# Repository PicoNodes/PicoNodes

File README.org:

* We have moved!

This project has a new home, over at https://gitlab.com/PicoNodes/PicoNodes

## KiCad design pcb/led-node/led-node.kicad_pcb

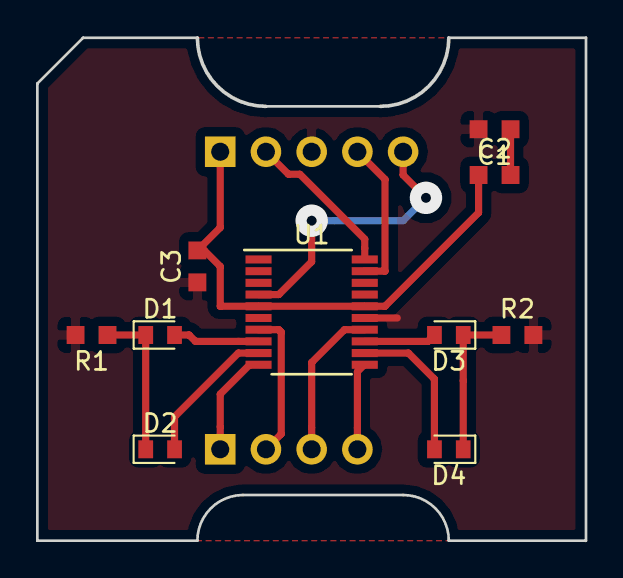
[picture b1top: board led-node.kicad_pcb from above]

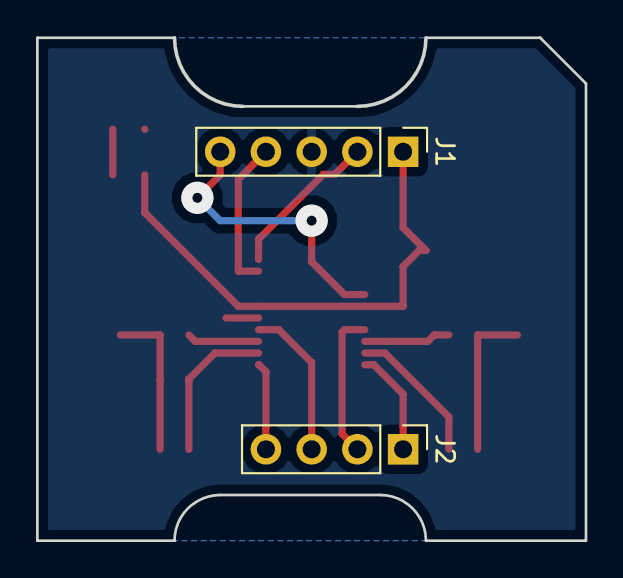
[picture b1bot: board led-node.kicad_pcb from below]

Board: 2 copper layers, 30.4 x 27.9 mm, 12 parts (2 on the bottom side), 16 nets.

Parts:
C1, C2: 100nF; C_0603_1608Metric_Pad0.99x1.00mm_HandSolder
C3: 10nF; C_0603_1608Metric_Pad0.99x1.00mm_HandSolder
D1: LED1; LED_0603_1608Metric_Pad0.82x1.00mm_HandSolder
D2: LED2; LED_0603_1608Metric_Pad0.82x1.00mm_HandSolder
D3: LED3; LED_0603_1608Metric_Pad0.82x1.00mm_HandSolder
D4: LED4; LED_0603_1608Metric_Pad0.82x1.00mm_HandSolder
J1: STM32_SWD; PinHeader_1x05_P2.54mm_Vertical
J2: PicoTalk; PinHeader_1x04_P2.54mm_Vertical
R1, R2: 100; R_0603_1608Metric_Pad0.99x1.00mm_HandSolder
U1: STM32F030F4Px; TSSOP-20_4.4x6.5mm_P0.65mm

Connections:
/Down: J2.1, U1.10
/Left: J2.2, U1.7
/Right: J2.4, U1.11
/SWCLK: J1.2, U1.20
/SWDIO: J1.4, U1.19
/Up: J2.3, U1.14
/nRST: J1.5, U1.4
GND: C1.2, C3.1, J1.3, R1.2, R2.2, U1.15
unnamed: C1.1, C2.2
unnamed: D1.1, D2.1, R1.1
unnamed: D1.2, U1.8
unnamed: D2.2, U1.9
unnamed: D3.1, D4.1, R2.1
unnamed: D3.2, U1.13
unnamed: D4.2, U1.12
VDD: C2.1, C3.2, J1.1, U1.5, U1.16

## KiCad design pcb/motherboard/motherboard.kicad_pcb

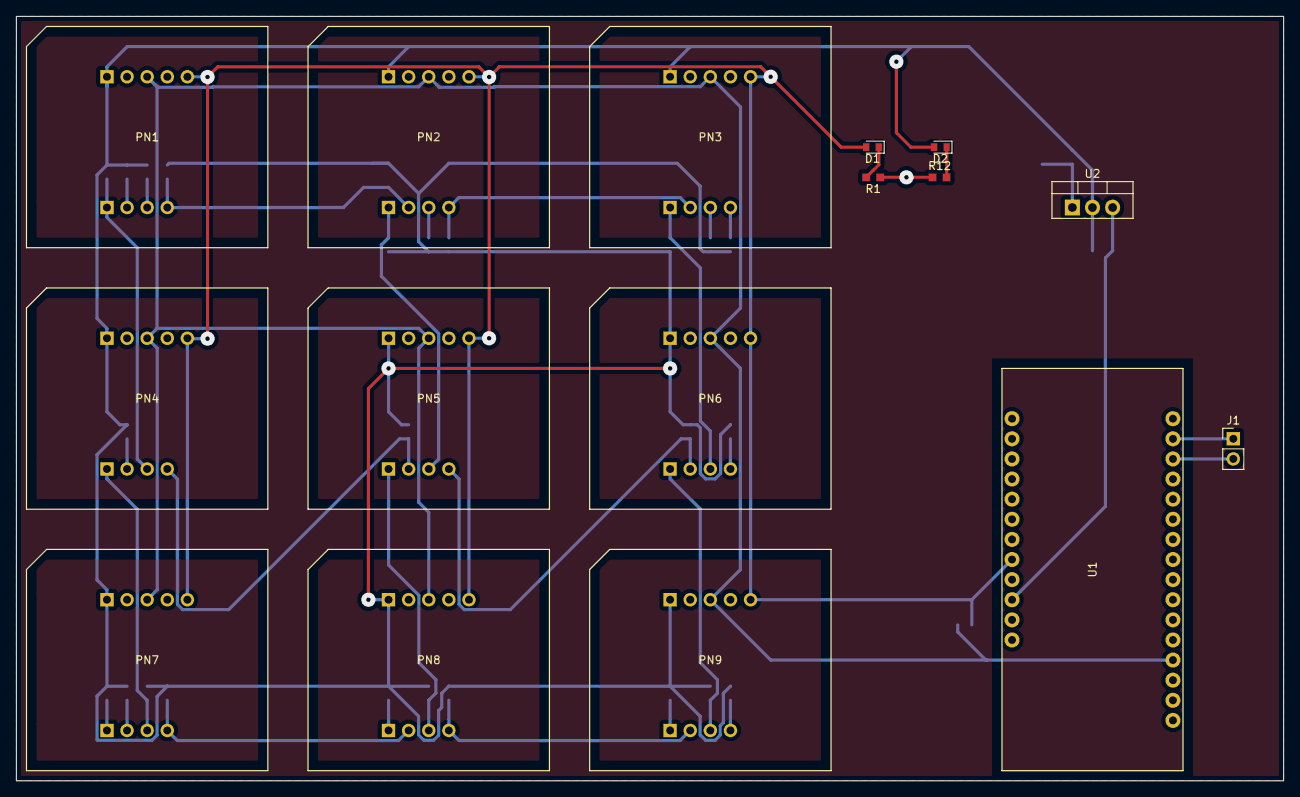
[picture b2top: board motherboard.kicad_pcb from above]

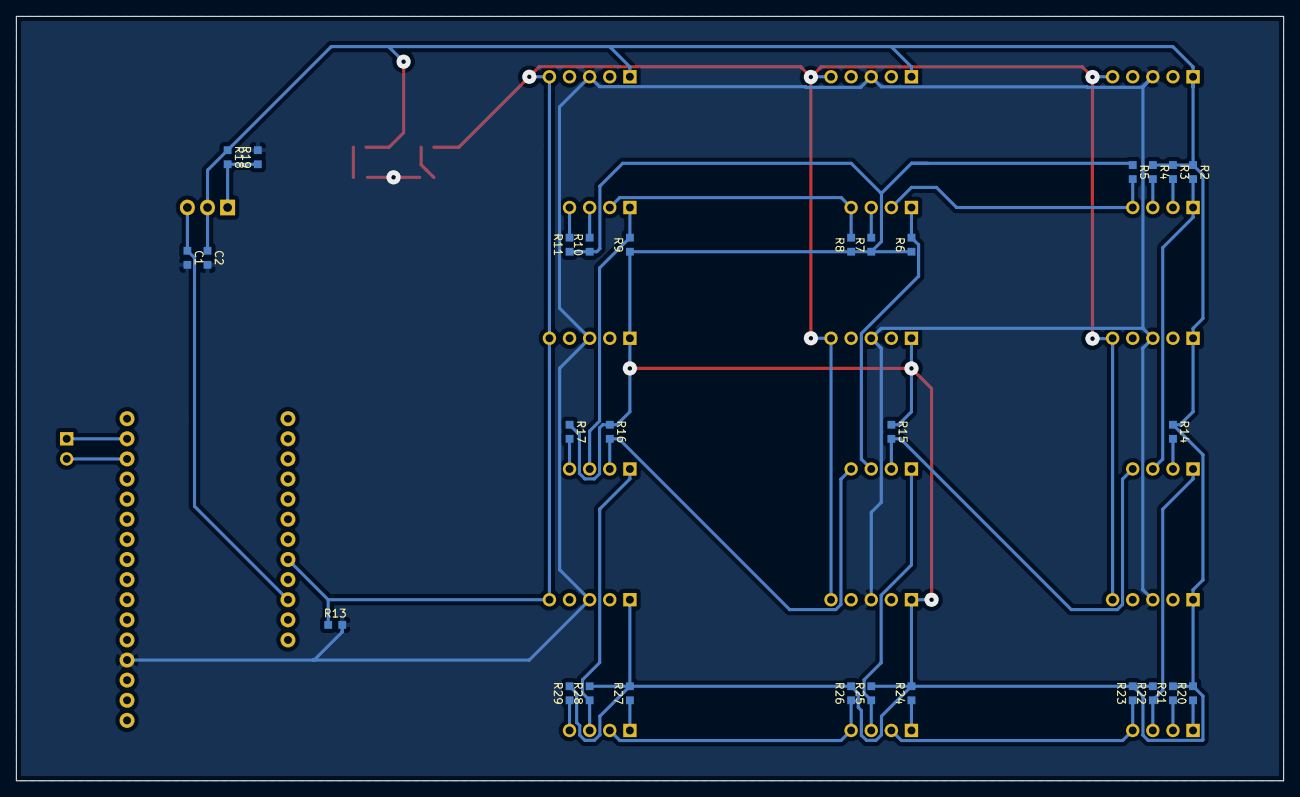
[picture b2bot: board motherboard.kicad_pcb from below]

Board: 2 copper layers, 160.0 x 96.5 mm, 45 parts (29 on the bottom side), 33 nets.

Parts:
C1: 0.1µF; C_0603_1608Metric_Pad0.99x1.00mm_HandSolder
C2: 1.0µF; C_0603_1608Metric_Pad0.99x1.00mm_HandSolder
D1: LED_Reset; LED_0603_1608Metric_Pad0.82x1.00mm_HandSolder
D2: LED_Vdd; LED_0603_1608Metric_Pad0.82x1.00mm_HandSolder
J1: UART; PinHeader_1x02_P2.54mm_Vertical
PN1, PN2, PN3, PN4, PN5, PN6, PN7, PN8, PN9: PicoNode-Socket-PH
R1, R12: 100; R_0603_1608Metric_Pad0.99x1.00mm_HandSolder
R2, R3, R4, R5, R6, R7, R8, R9, R10, R11, R14, R15, R16, R17, R20, R21, R22, R23, R24, R25, R26, R27, R28, R29: 4.7K; R_0603_1608Metric_Pad0.99x1.00mm_HandSolder
R13: 820; R_0603_1608Metric_Pad0.99x1.00mm_HandSolder
R18: 240; R_0603_1608Metric_Pad0.99x1.00mm_HandSolder
R19: 390; R_0603_1608Metric_Pad0.99x1.00mm_HandSolder
U1: Huzzah32; Adafruit_HUZZAH32
U2: LM317_3PinPackage; TO-220-3_Vertical

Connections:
/RX: J1.2, U1.26
/TX: J1.1, U1.27
/nReset: D1.2, PN1.5, PN2.5, PN3.5, PN4.5, PN5.5, PN6.5, PN7.5, PN8.5, PN9.5, R13.1, U1.5
GND: C1.2, C2.2, PN1.3, PN2.3, PN3.3, PN4.3, PN5.3, PN6.3, PN7.3, PN8.3, PN9.3, R1.1, R12.1, R13.2, R19.2, U1.16
unnamed: D1.1, R1.2
unnamed: D2.1, R12.2
unnamed: PN1.6, PN4.8, R2.2
unnamed: PN1.7, R3.2
unnamed: PN1.8, R4.2
unnamed: PN1.9, PN2.7, R5.2
unnamed: PN2.6, PN5.8, R6.2
unnamed: PN2.8, R7.2
unnamed: PN2.9, PN3.7, R8.2
unnamed: PN3.6, PN6.8, R9.2
unnamed: PN3.8, R10.2
unnamed: PN3.9, R11.2
unnamed: PN4.6, PN7.8, R22.1
unnamed: PN4.7, R14.2
unnamed: PN4.9, PN5.7, R15.2
unnamed: PN5.6, PN8.8, R25.1
unnamed: PN5.9, PN6.7, R16.2
unnamed: PN6.6, PN9.8, R28.1
unnamed: PN6.9, R17.2
unnamed: PN7.6, R20.1
unnamed: PN7.7, R21.1
unnamed: PN7.9, PN8.7, R23.1
unnamed: PN8.6, R24.1
unnamed: PN8.9, PN9.7, R26.1
unnamed: PN9.6, R27.1
unnamed: PN9.9, R29.1
unnamed: R18.2, R19.1, U2.1
VBUS: C1.1, U1.3, U2.3
VDD: C2.1, D2.2, PN1.1, PN2.1, PN3.1, PN4.1, PN5.1, PN6.1, PN7.1, PN8.1, PN9.1, R2.1, R3.1, R4.1, R5.1, R6.1, R7.1, R8.1, R9.1, R10.1, R11.1, R14.1, R15.1, R16.1, R17.1, R18.1, R20.2, R21.2, R22.2, R23.2, R24.2, R25.2, R26.2, R27.2, R28.2, R29.2, U2.2

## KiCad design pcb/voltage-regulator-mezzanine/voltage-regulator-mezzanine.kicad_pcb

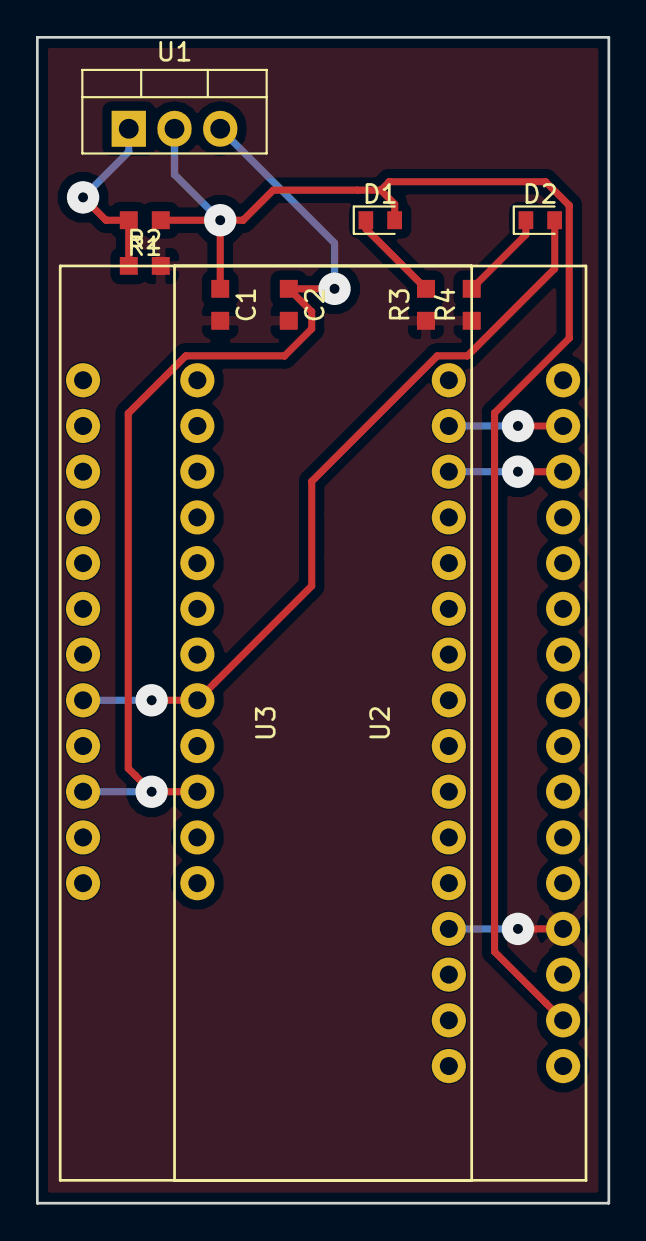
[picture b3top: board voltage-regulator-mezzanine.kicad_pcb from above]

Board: 2 copper layers, 31.8 x 64.8 mm, 11 parts (0 on the bottom side), 9 nets.

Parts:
C1: 1.0µF; C_0603_1608Metric_Pad0.99x1.00mm_HandSolder
C2: 0.1µF; C_0603_1608Metric_Pad0.99x1.00mm_HandSolder
D1: LED_vdd; LED_0603_1608Metric_Pad0.82x1.00mm_HandSolder
D2: LED_nReset; LED_0603_1608Metric_Pad0.82x1.00mm_HandSolder
R1: 240; R_0603_1608Metric_Pad0.99x1.00mm_HandSolder
R2: 390; R_0603_1608Metric_Pad0.99x1.00mm_HandSolder
R3, R4: 100; R_0603_1608Metric_Pad0.99x1.00mm_HandSolder
U1: LM317_3PinPackage; TO-220-3_Vertical
U2: Huzzah32_fake; Adafruit_HUZZAH32
U3: Huzzah32_real; Adafruit_HUZZAH32

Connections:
/Adj: R1.2, R2.1, U1.1
GND: C1.2, C2.2, R2.2, R3.1, R4.1, U2.16, U3.16
unnamed: D1.1, R3.2
unnamed: D2.1, R4.2
unnamed: D2.2, U2.5, U3.5
unnamed: U2.26, U3.26
unnamed: U2.27, U3.27
VBUS: C2.1, U1.3, U2.3, U3.3
VDD: C1.1, D1.2, R1.1, U1.2, U2.14

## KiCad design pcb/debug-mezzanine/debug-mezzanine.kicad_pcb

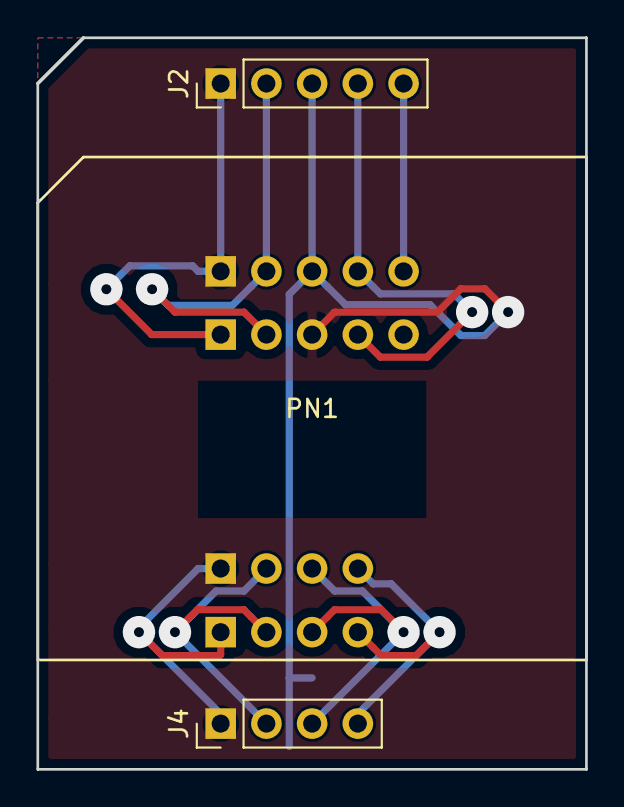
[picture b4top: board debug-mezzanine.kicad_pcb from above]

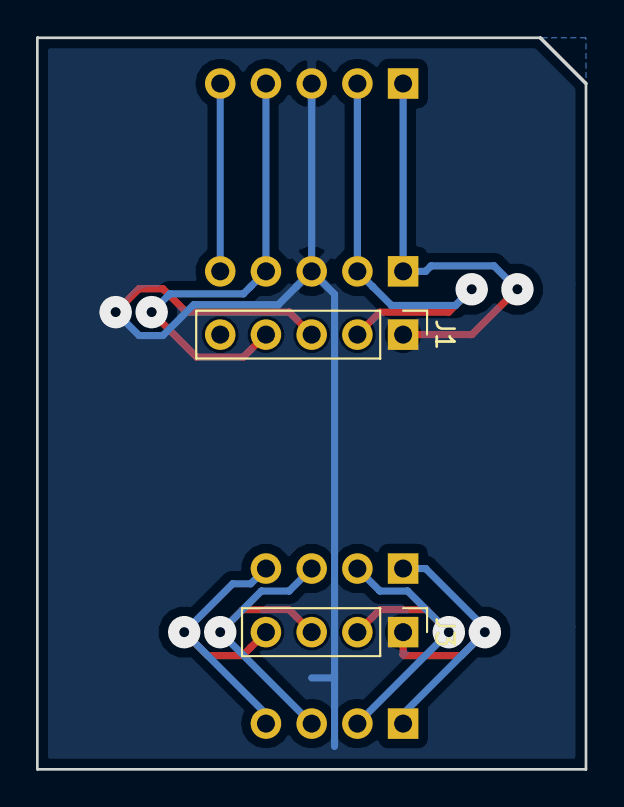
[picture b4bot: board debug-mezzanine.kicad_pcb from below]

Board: 2 copper layers, 30.5 x 40.6 mm, 5 parts (2 on the bottom side), 9 nets.

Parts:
J1, J2: STM32_SWD; PinHeader_1x05_P2.54mm_Vertical
J3, J4: PicoTalk; PinHeader_1x04_P2.54mm_Vertical
PN1: PicoNode-Socket-PH

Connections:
GND: J1.3, J2.3, PN1.3
unnamed: J1.2, J2.2, PN1.2
unnamed: J1.4, J2.4, PN1.4
unnamed: J2.5, PN1.5
unnamed: J3.1, J4.1, PN1.6
unnamed: J3.2, J4.2, PN1.7
unnamed: J3.3, J4.3, PN1.8
unnamed: J3.4, J4.4, PN1.9
VDD: J1.1, J2.1, PN1.1

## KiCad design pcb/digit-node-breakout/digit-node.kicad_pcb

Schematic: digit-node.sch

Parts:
C1, C2, C3: CP; C_0603_1608Metric
J1: Conn_01x09_Male; PinHeader_1x09_P2.54mm_Vertical
J2: STM32_SWD; PinHeader_1x05_P2.54mm_Vertical
Q1: BC847BS; SOT-363_SC-70-6
R1, R2: 100; R_0603_1608Metric
U1: STM32F030F4Px; TSSOP-20_4.4x6.5mm_P0.65mm

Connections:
/led_matrix/gnd_even: R2.1; also elsewhere on the board
/led_matrix/gnd_odd: R1.1; also elsewhere on the board
/led_matrix/led_01: U1.14; also elsewhere on the board
/led_matrix/led_23: U1.8; also elsewhere on the board
/led_matrix/led_45: U1.9; also elsewhere on the board
/led_matrix/led_67: U1.12; also elsewhere on the board
/led_matrix/led_89: U1.13; also elsewhere on the board
GND: C1.2, C3.2, J1.1, J2.3, Q1.1 (E1), Q1.4 (E2), U1.15
unnamed: C2.2, C3.1
unnamed: J1.4, U1.6
unnamed: J1.5, U1.3
unnamed: J1.6, U1.2
unnamed: J1.7, U1.7
unnamed: J1.8, U1.17
unnamed: J1.9, U1.18
unnamed: J2.2, U1.20
unnamed: J2.4, U1.19
unnamed: J2.5, U1.4
unnamed: Q1.2 (B1), U1.10
unnamed: Q1.3 (C2), R2.2
unnamed: Q1.5 (B2), U1.11
unnamed: Q1.6 (C1), R1.2
VDD: C1.1, J1.2, J2.1, U1.16
VDDA: C2.1, J1.3, U1.5

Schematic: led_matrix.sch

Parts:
D1: LED_0; LED_0603
D2: LED_1; LED_0603
D3: LED_2; LED_0603
D4: LED_3; LED_0603
D5: LED_4; LED_0603
D6: LED_5; LED_0603
D7: LED_6; LED_0603
D8: LED_7; LED_0603
D9: LED_8; LED_0603
D10: LED_9; LED_0603

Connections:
/led_matrix/gnd_even: D2.1, D4.1, D6.1, D8.1, D10.1; also elsewhere on the board
/led_matrix/gnd_odd: D1.1, D3.1, D5.1, D7.1, D9.1; also elsewhere on the board
/led_matrix/led_01: D1.2, D2.2; also elsewhere on the board
/led_matrix/led_23: D3.2, D4.2; also elsewhere on the board
/led_matrix/led_45: D5.2, D6.2; also elsewhere on the board
/led_matrix/led_67: D7.2, D8.2; also elsewhere on the board
/led_matrix/led_89: D9.2, D10.2; also elsewhere on the board

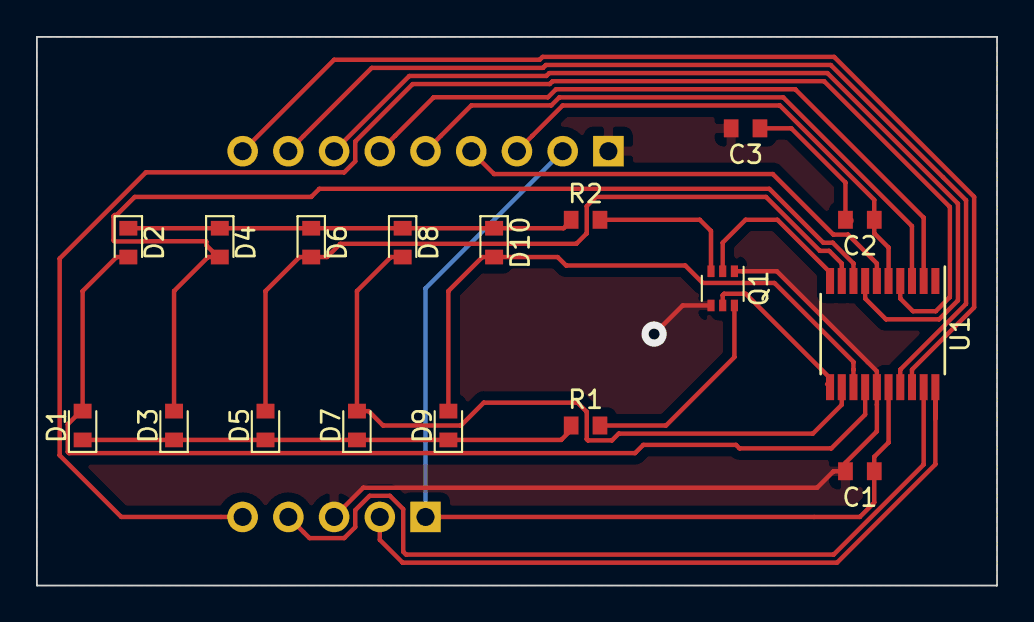
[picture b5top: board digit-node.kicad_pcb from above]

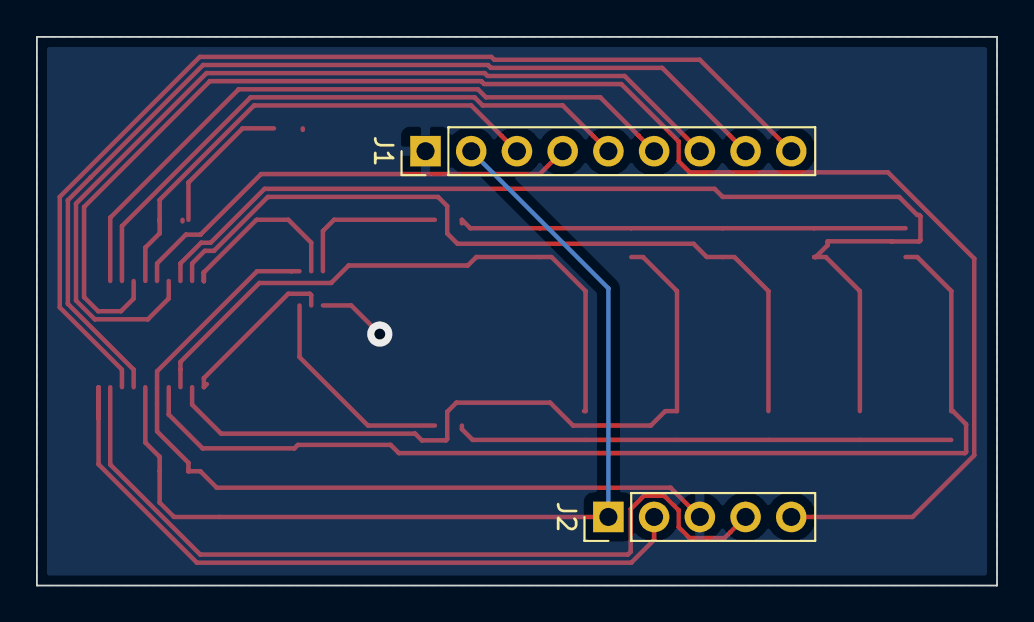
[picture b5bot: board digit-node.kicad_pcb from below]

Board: 2 copper layers, 53.3 x 30.5 mm, 19 parts (2 on the bottom side), 24 nets.

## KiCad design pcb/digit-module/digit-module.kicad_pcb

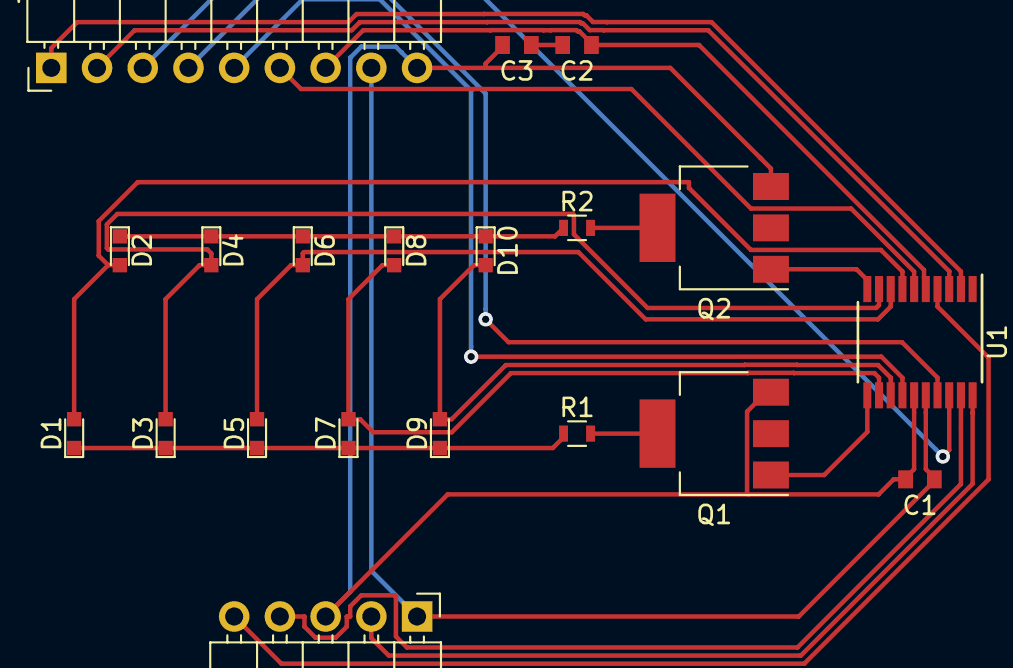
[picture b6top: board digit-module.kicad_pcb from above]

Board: 2 copper layers, 20 parts (0 on the bottom side), 24 nets.

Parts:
C1, C2, C3: CP; C_0603_1608Metric
D1: LED_0; LED_0603
D2: LED_1; LED_0603
D3: LED_2; LED_0603
D4: LED_3; LED_0603
D5: LED_4; LED_0603
D6: LED_5; LED_0603
D7: LED_6; LED_0603
D8: LED_7; LED_0603
D9: LED_8; LED_0603
D10: LED_9; LED_0603
J1: Conn_01x09_Male; PinHeader_1x09_P2.54mm_Horizontal
J2: STM32_SWD; PinHeader_1x05_P2.54mm_Horizontal
Q1, Q2: PZT2222A; SOT-223-3_TabPin2
R1, R2: 100; R_0603
U1: STM32F030F4Px; TSSOP-20_4.4x6.5mm_Pitch0.65mm

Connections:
/led_matrix/gnd_even: D2.1, D4.1, D6.1, D8.1, D10.1, R2.1
/led_matrix/gnd_odd: D1.1, D3.1, D5.1, D7.1, D9.1, R1.1
/led_matrix/led_01: D1.2, D2.2, U1.7
/led_matrix/led_23: D3.2, D4.2, U1.9
/led_matrix/led_45: D5.2, D6.2, U1.8
/led_matrix/led_67: D7.2, D8.2, U1.12
/led_matrix/led_89: D9.2, D10.2, U1.13
GND: C1.2, C3.2, J1.9, J2.3, Q1.3, Q2.3, U1.15
unnamed: C2.2, C3.1
unnamed: J1.1, U1.2
unnamed: J1.2, U1.3
unnamed: J1.3, U1.18
unnamed: J1.4, U1.17
unnamed: J1.5, U1.14
unnamed: J1.6, U1.6
unnamed: J2.2, U1.20
unnamed: J2.4, U1.19
unnamed: J2.5, U1.4
unnamed: Q1.1, U1.11
unnamed: Q1.2, R1.2
unnamed: Q2.1, U1.10
unnamed: Q2.2, R2.2
VDD: C1.1, J1.8, J2.1, U1.16
VDDA: C2.1, J1.7, U1.5

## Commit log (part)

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2018-03-19 Directory structure
2018-03-20 Added design notes and PCB sketch
2018-03-20 Moved design docs to docs folder
2018-03-20 ISA draft
2018-03-20 First prototype of assembler
2018-03-20 Allow empty lines, comments prototype
2018-03-21 Project structure for IDE
2018-03-21 greberfiler
    Alla gerberfiler som kan tänkas behövas för att fräsa PCB
2018-03-21 Started playing around with embedded rust for firmware
2018-03-21 Scala.js scaffolding
2018-03-22 Initial draft of UI that shows parser output and does light autoformatting
2018-03-22 Made autoformatting less overzealous
2018-03-23 Added outline for picoide server side, added support for stylesheets
2018-03-23 Monospace code editor
2018-03-26 Fixed the bytecode viewer
2018-03-26 Various cleanup
2018-03-26 Started playing around with node clients
2018-03-26 PCB and method in report
    beginning of method in the report
2018-03-26 More work on NodeServer
2018-03-27 Added a registry for connected nodes
2018-03-28 IDE: Use BooPickle for serialization
2018-03-29 IDE: Started integrating IDEClient
    Currently broken because Sink.actorRefWithAck causes linking errors,
    investigating alternative solutions
2018-03-29 IDE: Rewrote WSClient as a GraphStage instead of an Actor
2018-03-29 IDE: Sped up rebuild time dramatically
2018-03-29 Enable source maps, allow running in fullopt mode
2018-03-29 Cleaned up some side effects
2018-03-29 Added dependency graph plugin
2018-03-30 Removed a bunch of dead messages
2018-03-30 IDE: Heartbeats, don't hang after the first message
2018-03-30 IDE: Handle client-side event handling errors
2018-03-30 IDE: Don't beat so loudly
2018-03-30 Don't log raw IDE messages
2018-03-30 Implemented node list subscription
    Fixes #14
2018-03-31 Automatically subscribe to the node list
2018-03-31 Updated ENSIME
2018-03-31 Fixed Webpack refusing to build unless both fastopt and opt entrypoints were available
2018-03-31 Client-side board selection
2018-04-01 Kill the connection properly when the server fails to handle an incoming request
2018-04-01 Cleaned up build definition
2018-04-04 module and project updates
    module and report updates
2018-04-05 Swappable flow adapter
2018-04-05 Migrated to a separate IDECommandHandler stage
2018-04-05 Renamed all references for Programmers to Downloaders, according to #15
2018-04-05 Don't show the downloader change before it's actually done
2018-04-05 More lenses
2018-04-09 Syntax highlighting
2018-04-10 Added terminology document, fixes #15
2018-04-10 Cleaned up terminology doc a bit
2018-04-11 testcodes and dic
    for mcu questionformular
2018-04-11 LED blinker for F0 MCU
2018-04-11 Clarify the role of PicoStorm
2018-04-11 docs
    architecture, picture of comflow
2018-04-11 Added downloader version command/event
2018-04-11 Moved platform architecture diagram to Ditaa
2018-04-11 Mention the IDE in the platform architecture diagram
    Fixes #10
2018-04-11 Get rid of Word architecture diagram
2018-04-11 UX for downloading a program
2018-04-11 Support for emitting DownloadBytecode DownloaderCommands
2018-04-12 Added page 2 of questionaire
2018-04-13 Emacs: don't build tests for blinky
2018-04-13 Moved stm32f0x0 to https://github.com/PicoNodes/stm32f0x0
2018-04-13 Renamed BoardPicker to DownloaderPicker
2018-04-13 Imported ESP32 hello world
2018-04-13 Started playing around with downloader
2018-04-14 Register- and libfile
    Started the actionfunctions for the intructions. This file compile :)
2018-04-14 Reg- and libfile
    I forgot to save. This is compiling
2018-04-14 Ok this is going to compile!
    last try
2018-04-16 Got rid of some hello world code in the downloader
2018-04-16 Ignore more temp files from ESP-IDF
2018-04-16 Repport
    The methology chapter, an introduction.
2018-04-16 Diode-React has now released a ScalaJS-React 1.2 build, so we no longer need to rebuild it ourselves
2018-04-16 Couple error handling for DownloaderServer
2018-04-16 TLS for Server<->Downloader communication
2018-04-16 Split up picoserver according to a rough layer structure
2018-04-17 Report
    Methology chapter
2018-04-17 TLSClientAuthStage: Don't double-pull
2018-04-17 Background
    Making a summery of studies made for the implementation of datalogical
    thinking and programming in scool.
2018-04-17 Fixed downloaders being deregistered immediately
2018-04-17 Added pseudocode implementations of instructions to ISA
2018-04-17 Implemented the other instructions in the assembler
2018-04-17 Reenabled BytecodeViewer, see #25
2018-04-17 Show errors inline, see #25
2018-04-17 Report
    Background
2018-04-17 Show widgets for all errors, not just the first, fixes #25
2018-04-17 Styling for assembler errors
2018-04-17 Disabled BytecodeViewer
2018-04-17 Netclient can now connect and auth
2018-04-17 Refactored netclient to be easier to integrate
2018-04-17 Don't build main for standalone netclient
2018-04-17 picorunner.rs
    Work on func run instruction
2018-04-17 netclient on ESP32 now sorta kinda maybe works
2018-04-18 Report
    Report
2018-04-18 Server<->Downloader communication is also PicoStorm
2018-04-18 New doc
    Digitaliseringskommisionens statliga utredning om att digitalisera
    Sverige och med det IT-politiska målet att göra Sverige bäst i världen
    på att använda digitaliseringen möjligheter.
2018-04-18 Timeout for downloaders that are stuck authenticating
2018-04-18 Renamed hello_world_main.c
2018-04-18 MCU programming
    Work on the interpreter and running instructions. This compile. Next is
    to make testfunctions to see evrything run correctly
2018-04-18 Added read function to netclient
2018-04-18 Downloader can now communicate over UART!
2018-04-19 Instructions and PicoTalk
    Finnished the program for running the instructions and started
    documenting PicoTalk protocol.
2018-04-19 Started the domcs for PicoTalk protocol
2018-04-19 Integrated timing diagram into PicoTalk.org
2018-04-19 Finished PicoTalk timing diagram
2018-04-19 Implemented opendrainy in terms of the HAL
2018-04-19 Starting write to pin. Compiling
2018-04-20 Spellcheck
2018-04-20 PicoStorm: added support for writing events
2018-04-20 Described PicoStorm so far
    Fixes #22
2018-04-20 Compiles
2018-04-20 Attempted to rewrite opendrainy using RTFM
2018-04-20 Removed some test data
2018-04-23 Fixed opendrainy-rtfm not firing USART interrupts
2018-04-23 arithOp should be 1 for sub, not 0
2018-04-23 PicoStorm: Report invalid message IDs
2018-04-23 Print received PicoStorm commands
2018-04-23 Mention empty PicoStorm messages in the spec
2018-04-23 PicoStorm ping messages, fixes #27
2018-04-24 Updated client keys to follow the new DN scheme
2018-04-24 Downloader labels!
2018-04-24 Finnished reading pin. Compiles
2018-04-27 Added Picotalk transmitter FSM
2018-04-27 Transmit statemachine
2018-04-27 Added piconode-compute and picostore subprojects
2018-04-27 Moving main to piconode-compute
2018-04-27 Writing to flash sorta kinda works, ish
2018-04-30 Fixed flash memory writes
    Fixes #29
2018-04-30 Renamed USART1 task to something more appropriate
2018-04-30 Naming cleanup
2018-04-30 Forward checksum to IDE
    See #32
2018-04-30 Moved breakout board to separate subfolder
2018-04-30 Added Digit Node schematic draft
2018-05-01 Renamed digit-module for consistency
2018-05-01 More digit PCB cleanup
2018-05-01 Digit PCB is now 100% via-free!
2018-05-01 Even more compact!
2018-05-01 Oops.. missed a stale track screwing with things
2018-05-01 Blacklisted more backup files
2018-05-01 Ground planes
2018-05-01 Board outline
2018-05-01 Documented how to get STL files out of KiCad
2018-05-02 PCB cavity for enclosure
2018-05-02 Finnish Recieve machine state. This compiles
2018-05-02 Use a transistor array instead of two discrete transistors
2018-05-02 updates on recieve fn. Compiles
    May add changes to add a last state. Transmission done with the recieved
    value
2018-05-02 module for more flash pcb. Not tested
2018-05-03 Some comments on the pico-commpute srcfile
2018-05-03 Adapted PCB for Mentorspace mill design rules
2018-05-04 Finnished picotalk and started node communication task and path
2018-05-04 Piconodes test tasks
2018-05-04 Digit demo
2018-05-07 Started working on a the node motherboard...
2018-05-07 Adopted compute node PCB to use pin headers
    Since we currently don't have any 1mm PCB stock to use
2018-05-07 LED and button node PCBs
2018-05-07 Try for transmit and recieve. This do not work
2018-05-08 Fixed invalid diagrams
2018-05-08 Communication protocol
    Compiles and uses 10k Hz
2018-05-08 Started merging the compute node code
2018-05-08 Increased auth timeout
2018-05-08 More integration stuff
2018-05-08 Node-programmer
2018-05-08 piconode-led
2018-05-08 Pin orientation
2018-05-09 More convenient flashing
2018-05-09 Converted prog_counter to usize
2018-05-10 datasheet for the piconode-led
2018-05-10 File browser
2018-05-10 Spelling
2018-05-11 User manual for the piconode-switch
2018-05-11 Prepared piconode-led and -switch for the "real" node boards
2018-05-14 Made PicoNode-LED resync the PicoTalk clock at the beginning of each message
    This allows stable communication at 10kHz
2018-05-14 Debug mezzanine PCB
2018-05-14 user example
    Doc procoded with example for the user to program one piconode and use
    it with the lednode and the switchnode
2018-05-15 iomem instructions
2018-05-15 Use the ground plane, Luke!
2018-05-15 Fixed a race condition in LED<->Switch communication
2018-05-16 Moved rename to clicking the name
2018-05-16 Suggest saving before switching file
2018-05-16 Made the save prompt (slightly) prettier
2018-05-16 Added a prompt when trying to leave without saving
2018-05-16 Updated dependencies
2018-05-16 Factored out modality to a separate component
2018-05-16 Fixed "ghost" errors appearing when opening files
    Fixes #36
2018-05-16 Reformat the current line on blur
2018-05-16 Reduced log spam
2018-05-17 Bring our own voltage regulator instead of using the Huzzah32's built-in
2018-05-17 Via optimization
2018-05-17 Track cleanup
2018-05-17 Nicer motherboard markings
2018-05-17 We definitely need a heat sink...
2018-05-17 IGNORE
2018-05-18 picoregister
    modified the register to integrate the system
2018-05-18 picorunner
2018-05-18 Make the DRC happy
2018-05-18 Moved LED node text
2018-05-18 Voltage regulator mezzanine
    Got to bodge it since we don't have the PCB area to make another new motherboard
    Vbus is still forwarded, so it will still work (although have no real use) with
    the new motherboard
2018-05-21 Added label to the current file name
2018-05-21 user manual for piconode-compute
2018-05-21 baudrate to 4000
2018-05-21 compute-node exercises
2018-05-21 Exercises formatting
2018-05-22 Various desperate troubleshooting
2018-05-22 PN-switch spellcheck
2018-05-22 More spellchecking
2018-05-22 tillståndsmall
2018-05-22 Reset message
2018-05-22 Auto-detect the websocket URL
2018-05-23 report
2018-05-23 Changed SERVER_ADDR to the windows default ICS IP
2018-05-24 Fixed SERVER_ADDR
2018-05-24 Various proofreading, and started working on prior art
2018-05-25 Fleshed out prior art
2018-05-25 Report stuff
2018-05-25 Started working on the method
2018-05-29 Fixed serial numbers
2018-05-29 Made PicoStore a proper singleton
2018-05-29 Increased picotalk frequency to 10kHz
2018-05-29 Moved method to a separate heading
2018-05-29 Added communication layout
2018-05-29 Discuss the node design
2018-05-29 Result documentation
2018-05-29 Ethics
2018-05-30 Document picotalk and picoasm
2018-05-30 PicoIDE chapter
2018-05-30 more acronyms
2018-05-31 Various review stuff from yesterday
2018-06-01 Revert "report"
    This reverts commit 446f81553375c85bec26f4db23a6565ebc664199.
2018-06-01 Analysis stuff
2018-06-01 Ignore minted
2018-06-01 Power usage documentation
2018-06-01 Dropped power usage calculations
2018-06-01 Further opportunities
2018-06-01 More proofreading
2018-06-04 More proofreading, how fun
2018-06-04 Add source Nationall digitalisation
2018-06-04 Took of comment
2018-06-04 Included manuals in report
